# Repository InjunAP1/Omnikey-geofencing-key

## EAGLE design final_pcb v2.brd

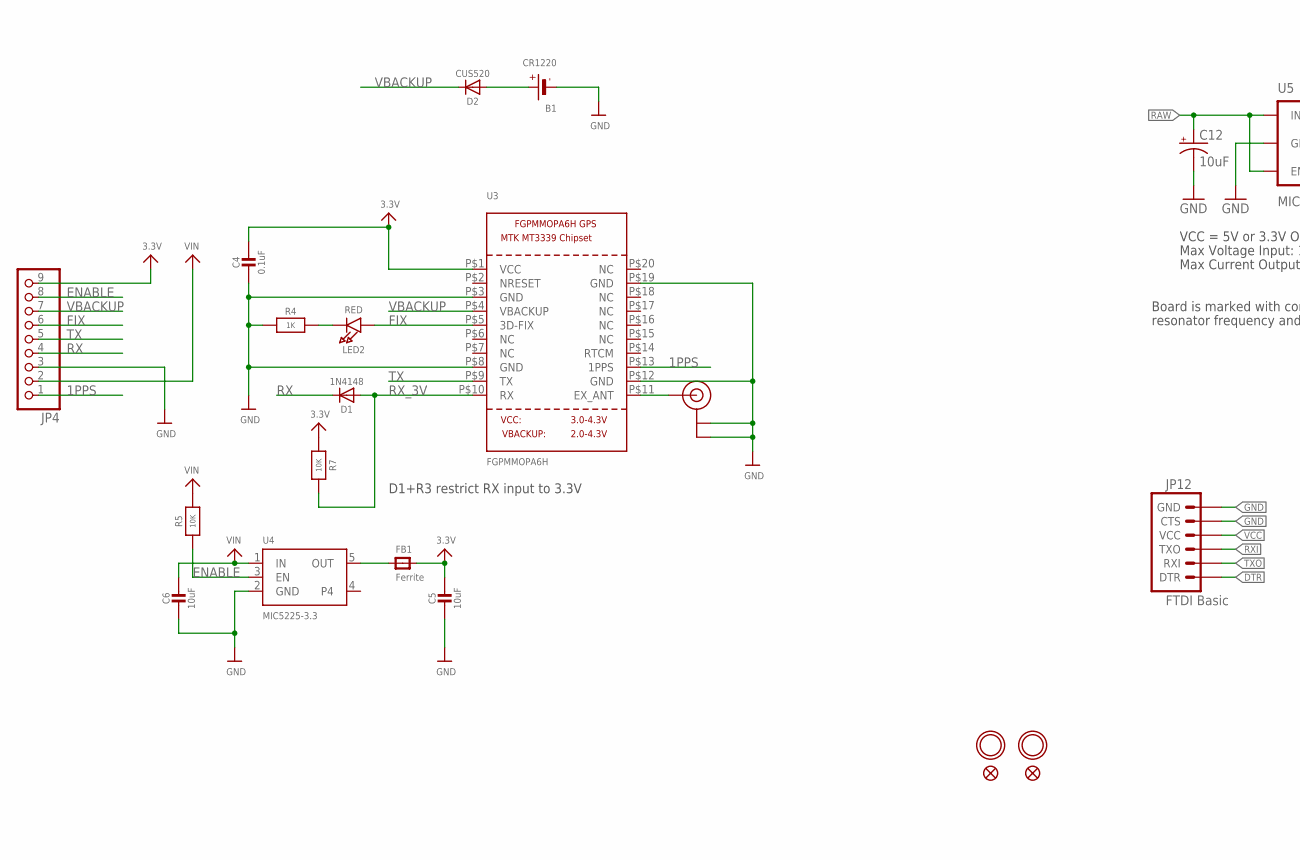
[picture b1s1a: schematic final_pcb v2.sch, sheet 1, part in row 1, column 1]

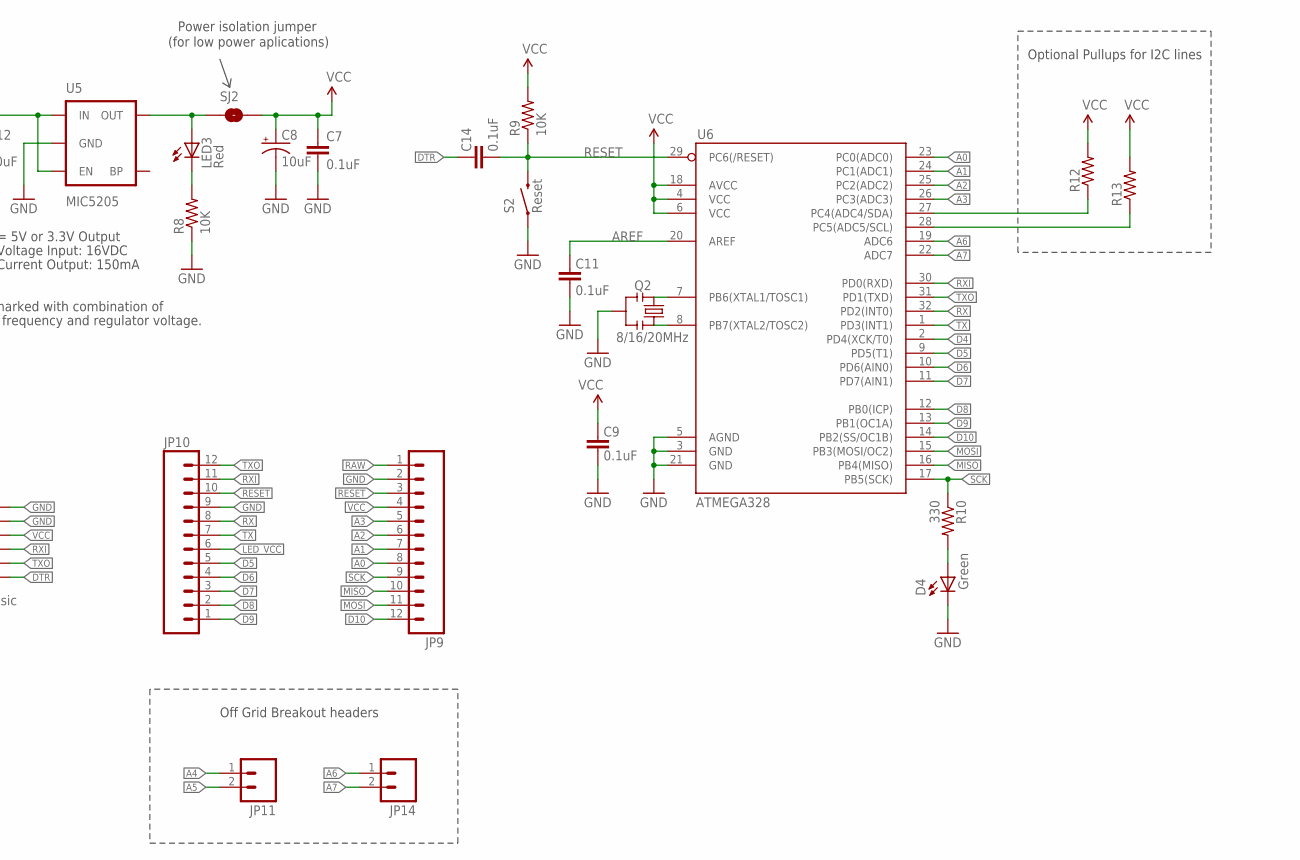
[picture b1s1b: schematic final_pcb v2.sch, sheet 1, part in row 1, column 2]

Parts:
B1: CR1220
C4: 0.1uF; 0805-NO
C5, C6: 10uF; 0805-NO
C7, C9, C11, C14: 0.1uF; 0603-CAP
C8, C12: 10uF; EIA3216
D1: 1N4148; SOD-323
D2: CUS520; SOD-323
D4: Green; 0603-LED-ALT1
FB1: Ferrite; 0805-NO
FID1, FID2: FIDUCIAL""; FIDUCIAL_1MM
JP4: HEADER-1X970MIL; 1X09_ROUND_70
JP9, JP10: M12PTH; 1X12
JP11, JP14: M02PTH; 1X02
JP12: FTDI Basic; 1X06
LED2: RED; CHIPLED_0805
LED3: Red; 0603-LED-ALT1
Q2: 8/16/20MHz; RESONATOR-SMD-1:1
R4: 1K; 0805-NO
R5, R7: 10K; 0805-NO
R8, R9: 10K; 0603-RES
R10: 330; 0603-RES
R12, R13: RESISTOR0603-RES; 0603-RES
S2: Reset; TACTILE-SWITCH-SMD-ALT01
SJ2: SOLDERJUMPERNC; SJ_2S
U3: FGPMMOPA6H
U4: MIC5225-3.3; SOT23-5
U5: MIC5205; SOT23-5
U6: ATMEGA328; TQFP32-08
U$10, U$12: MOUNTINGHOLE2.5; MOUNTINGHOLE_2.5_PLATED
U$20: U.FL

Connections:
1PPS: JP4.1, U3.P$13 (1PPS)
3.3V: C4.1, C5.1, FB1.2, JP4.9, R7.1, U3.P$1 (VCC)
A0: JP9.8, U6.23 (PC0(ADC0))
A1: JP9.7, U6.24 (PC1(ADC1))
A2: JP9.6, U6.25 (PC2(ADC2))
A3: JP9.5, U6.26 (PC3(ADC3))
A4: JP11.1, R12.1, U6.27 (PC4(ADC4/SDA))
A5: JP11.2, R13.1, U6.28 (PC5(ADC5/SCL))
A6: JP14.1, U6.19 (ADC6)
A7: JP14.2, U6.22 (ADC7)
AREF: C11.2, U6.20 (AREF)
D4: U6.2 (PD4(XCK/T0))
D5: JP10.5, U6.9 (PD5(T1))
D6: JP10.4, U6.10 (PD6(AIN0))
D7: JP10.3, U6.11 (PD7(AIN1))
D8: JP10.2, U6.12 (PB0(ICP))
D9: JP10.1, U6.13 (PB1(OC1A))
D10: JP9.12, U6.14 (PB2(SS/OC1B))
DTR: C14.2, JP12.1 (DTR)
ENABLE: JP4.8, R5.1, U4.3 (EN)
FIX: JP4.6, LED2.A, U3.P$5 (3D-FIX)
GND: B1.-, C4.2, C5.2, C6.2, C7.2, C8.C (-), C9.1, C11.1, C12.C (-), D4.C, JP4.3, JP9.2, JP10.9, JP12.5 (CTS), JP12.6 (GND), Q2.2, R4.1, R8.1, S2.1, S2.2 (1), U3.P$3 (GND), U3.P$8 (GND), U3.P$12 (GND), U3.P$19 (GND), U4.2 (GND), U5.2 (GND), U6.3 (GND), U6.5 (AGND), U6.21 (GND), U$20.P$1 (GND), U$20.P$2 (GND); also elsewhere on the board
LED_VCC: JP10.6; also elsewhere on the board
MISO: JP9.10, U6.16 (PB4(MISO))
MOSI: JP9.11, U6.15 (PB3(MOSI/OC2))
unnamed: FB1.1, U4.5 (OUT)
unnamed: LED2.C, R4.2
unnamed: U3.P$11 (EX_ANT), U$20.P$3 (SIGNAL)
unnamed: B1.+$1 (+), B1.+$2 (+), D2.A
unnamed: D4.A, R10.2
unnamed: Q2.3, U6.8 (PB7(XTAL2/TOSC2))
unnamed: Q2.1, U6.7 (PB6(XTAL1/TOSC1))
unnamed: LED3.A, SJ2.1, U5.5 (OUT)
unnamed: LED3.C, R8.2
RAW: C12.A (+), JP9.1, U5.1 (IN), U5.3 (EN)
RESET: C14.1, JP9.3, JP10.10, R9.1, S2.3 (2), S2.4 (2), U6.29 (PC6(/RESET))
RX: D1.C, JP4.4, JP10.8, U6.32 (PD2(INT0))
RXI: JP10.11, JP12.3 (TXO), U6.30 (PD0(RXD))
RX_3V: D1.A, R7.2, U3.P$10 (RX)
SCK: JP9.9, R10.1, U6.17 (PB5(SCK))
TX: JP4.5, JP10.7, U3.P$9 (TX), U6.1 (PD3(INT1))
TXO: JP10.12, JP12.2 (RXI), U6.31 (PD1(TXD))
VBACKUP: D2.C, JP4.7, U3.P$4 (VBACKUP)
VCC: C7.1, C8.A (+), C9.2, JP9.4, JP12.4 (VCC), R9.2, R12.2, R13.2, SJ2.2, U6.4 (VCC), U6.6 (VCC), U6.18 (AVCC)
VIN: C6.1, JP4.2, R5.2, U4.1 (IN)

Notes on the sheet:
D1+R3 restrict RX input to 3.3V
Max Voltage Input: 16VDC
Max Current Output: 150mA
Board is marked with combination of
resonator frequency and regulator voltage.
VCC = 5V or 3.3V Output
Optional Pullups for I2C lines
Off Grid Breakout headers
Power isolation jumper
(for low power aplications)

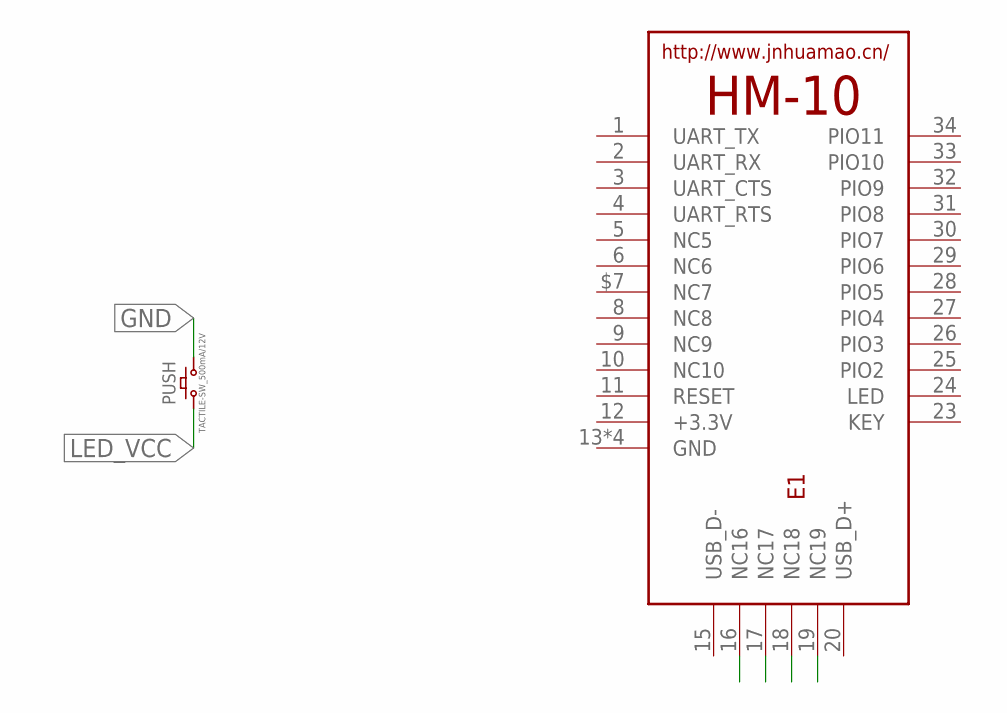
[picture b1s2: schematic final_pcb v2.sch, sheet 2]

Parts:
E1: HM-10-BOARD; 26.9X13X2.2_BOARD
PUSH: TACTILE-SW_500mA/12V; BTN_MOMENTARY_SPST-NO_SMD_12V_50MA_L5.2-W5.2

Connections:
GND: PUSH.3 (2); also elsewhere on the board
LED_VCC: PUSH.1; also elsewhere on the board

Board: 2 copper layers, 44 parts (0 on the bottom side), 44 nets, no tracks yet.

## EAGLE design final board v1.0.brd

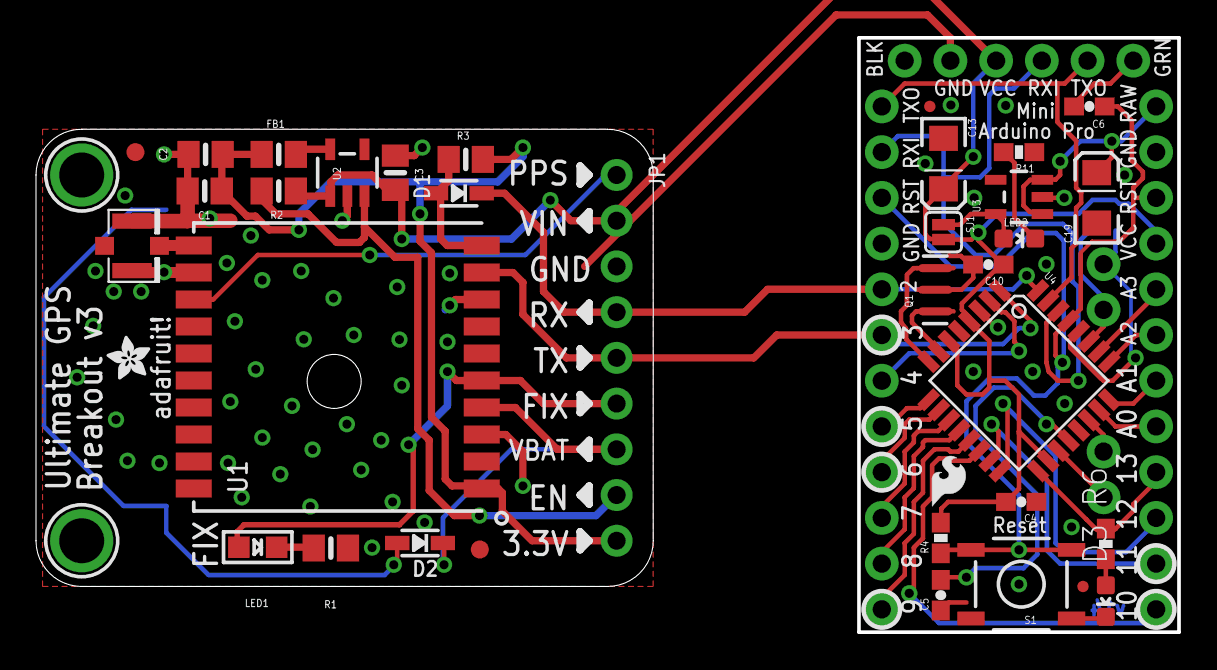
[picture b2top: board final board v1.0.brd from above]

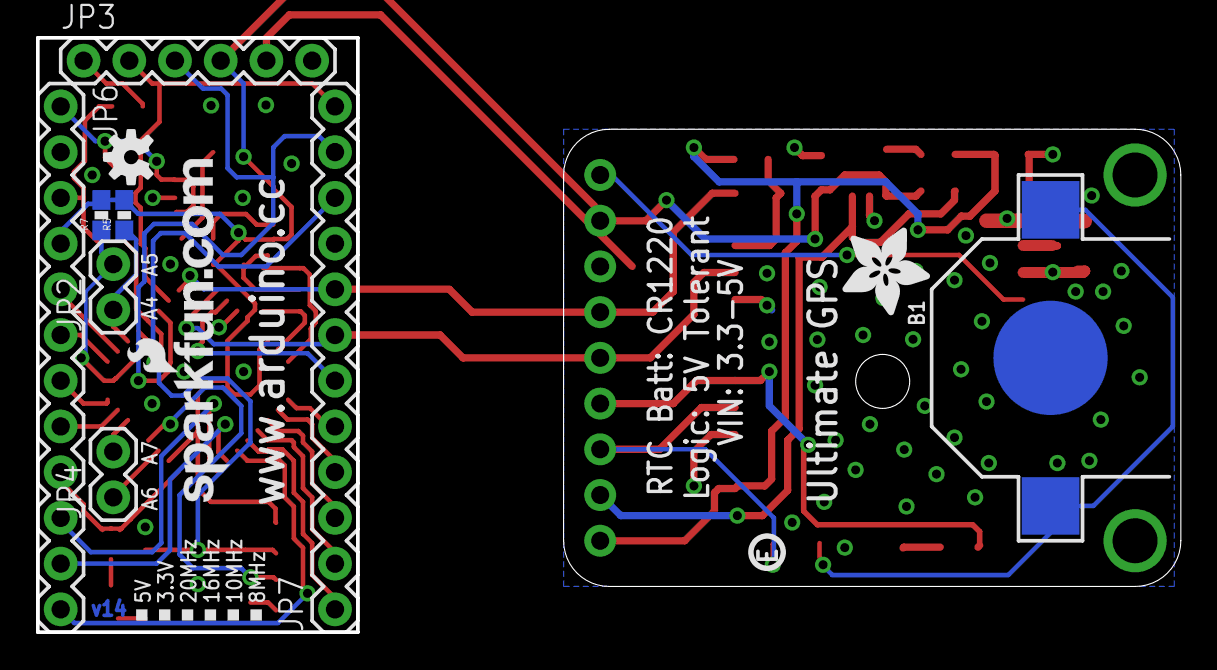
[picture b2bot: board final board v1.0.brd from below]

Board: 2 copper layers, 63.4 x 33.0 mm, 50 parts (12 on the bottom side), 44 nets.

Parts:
B1: CR1220
C1: 0.1uF; 0805-NO
C2, C3: 10uF; 0805-NO
C4, C5, C6, C10: 0.1uF; 0603-CAP
C13, C19: 10uF; EIA3216
D1: 1N4148; SOD-323
D2: CUS520; SOD-323
D3: Green; 0603-LED-ALT1
FB1: Ferrite; 0805-NO
FID1, FID2: FIDUCIAL""; FIDUCIAL_1MM
JP1: 1X09_ROUND_70
JP2, JP4: 1X02
JP3: FTDI Basic; 1X06
JP5, JP8: FIDUCIALUFIDUCIAL; MICRO-FIDUCIAL
JP6, JP7: 1X12
LED1: RED; CHIPLED_0805
LED2: Red; 0603-LED-ALT1
Q1: 8/16/20MHz; RESONATOR-SMD-1:1
R1: 1K; 0805-NO
R2, R3: 10K; 0805-NO
R4, R11: 10K; 0603-RES
R5, R7: 0603-RES
R6: 330; 0603-RES
S1: Reset; TACTILE-SWITCH-SMD-ALT01
SJ1: SJ_2S
U1: FGPMMOPA6H
U2: MIC5225-3.3; SOT23-5
U3: MIC5205; SOT23-5
U4: ATMEGA328; TQFP32-08
U$1: LOGO-SFESK; SFE-LOGO-FLAME
U$3: OSHW-LOGOS; OSHW-LOGO-S
U$8, U$9: MOUNTINGHOLE2.5; MOUNTINGHOLE_2.5_PLATED
U$11: LOGO-SFENEW; SFE-NEW-WEBLOGO
U$15: ADAFRUIT_2.5MM
U$16: PCBFEAT-REV-040
U$18: ADAFRUIT_5MM
U$20: U.FL

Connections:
1PPS: JP1.1, U1.P$13
3.3V: C1.1, C2.1, FB1.2, JP1.9, R3.1, U1.P$1
A0: JP6.8, U4.23
A1: JP6.7, U4.24
A2: JP6.6, U4.25
A3: JP6.5, U4.26
A4: JP2.1, R5.1, U4.27
A5: JP2.2, R7.1, U4.28
A6: JP4.1, U4.19
A7: JP4.2, U4.22
AREF: C5.2, U4.20
D4: JP7.6, U4.2
D5: JP7.5, U4.9
D6: JP7.4, U4.10
D7: JP7.3, U4.11
D8: JP7.2, U4.12
D9: JP7.1, U4.13
D10: JP6.12, U4.14
DTR: C6.2, JP3.1
ENABLE: JP1.8, R2.1, U2.3
FIX: JP1.6, LED1.A, U1.P$5
GND: B1.-, C1.2, C2.2, C3.2, JP1.3, R1.1, U1.P$3, U1.P$8, U1.P$12, U1.P$19, U2.2, U$20.P$1, U$20.P$2
GND1: C4.1, C5.1, C10.2, C13.C, C19.C, D3.C, JP3.5, JP3.6, JP6.2, JP7.9, Q1.2, R11.1, S1.1, S1.2, U3.2, U4.3, U4.5, U4.21
MISO: JP6.10, U4.16
MOSI: JP6.11, U4.15
unnamed: B1.+$1, B1.+$2, D2.A
unnamed: LED1.C, R1.2
unnamed: FB1.1, U2.5
unnamed: U1.P$11, U$20.P$3
unnamed: Q1.3, U4.8
unnamed: Q1.1, U4.7
unnamed: D3.A, R6.2
unnamed: LED2.A, SJ1.1, U3.5
unnamed: LED2.C, R11.2
RAW: C19.A, JP6.1, U3.1, U3.3
RESET: C6.1, JP6.3, JP7.10, R4.1, S1.3, S1.4, U4.29
RX: D1.C, JP1.4, JP7.8, U4.32
RXI: JP3.3, JP7.11, U4.30
RX_3V: D1.A, R3.2, U1.P$10
SCK: JP6.9, R6.1, U4.17
TX: JP1.5, JP7.7, U1.P$9, U4.1
TXO: JP3.2, JP7.12, U4.31
VBACKUP: D2.C, JP1.7, U1.P$4
VIN: C3.1, C4.2, C10.1, C13.A, JP1.2, JP3.4, JP6.4, R2.2, R4.2, R5.2, R7.2, SJ1.2, U2.1, U4.4, U4.6, U4.18

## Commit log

2019-11-14 Create driver_v1
    This is for the omnikey project back in Spring 2019. The code is still original from that time and has not been modified
2020-05-22 Conceptual PCB files for stepper motor wiring via EAGLE pcb design software
    These boards were initially to be hard wired to a custom PCB and while the designs were ready to be printed, we did not have time to order them.
    Also note, included Arduino Pro Mini and Adafruit Ultimate GPS board files as they were also used and not available natively on EAGLE.

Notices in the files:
parts and their libraries:
SparkFun-Passives: Licensing: CC v3.0 Share-Alike You are welcome to use this library for commercial purposes.
